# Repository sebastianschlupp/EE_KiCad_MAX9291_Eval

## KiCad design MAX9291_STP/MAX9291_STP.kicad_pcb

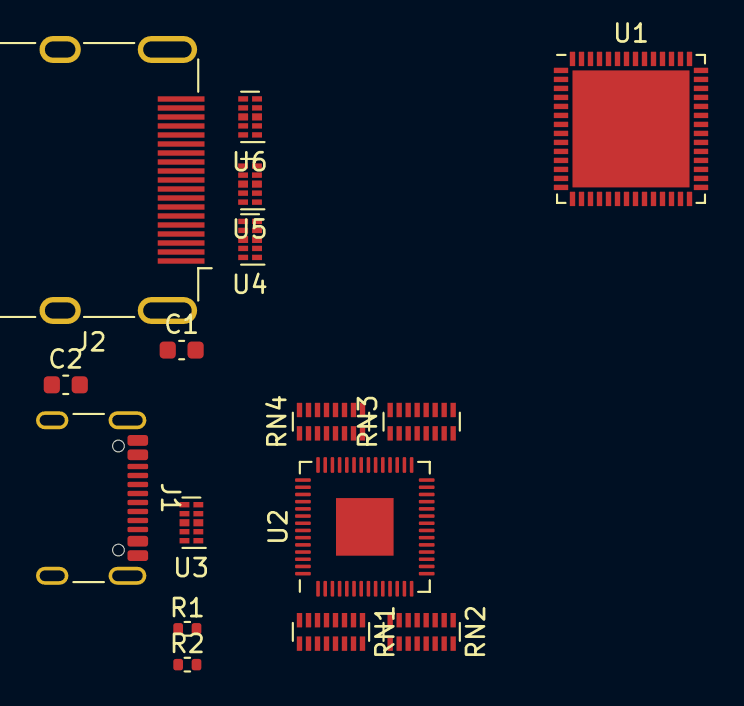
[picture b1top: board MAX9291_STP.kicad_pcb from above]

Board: 2 copper layers, 16 parts (0 on the bottom side), 53 nets, no tracks yet.

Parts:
C1, C2: C; C_0603_1608Metric
J1: USB_C_Receptacle; USB_C_Receptacle_GCT_USB4105-xx-A_16P_TopMnt_Horizontal
J2: HDMI_A_1.4; HDMI_A_Molex_208658-1001_Horizontal
R1, R2: 5.1k; R_0402_1005Metric
RN1, RN2, RN3, RN4: 4.7K; Yageo_YC248
U1: MAX9291; TQFN-56-1EP_8x8mm_P0.5mm_EP6.5x6.5mm
U2: RP2040; QFN-56-1EP_7x7mm_P0.4mm_EP3.2x3.2mm
U3, U4, U5, U6: TPD4E02B04DQA; USON-10_2.5x1.0mm_P0.5mm

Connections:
GNDREF: C1.2, C2.2, J1.A1 (GND), J1.A12 (GND), J1.B1 (GND), J1.B12 (GND), J2.17 (GND), R1.2, R2.2, U1.57 (GND), U2.57 (GND), U3.3 (G), U3.8 (G), U4.3 (G), U4.8 (G), U5.3 (G), U5.8 (G), U6.3 (G), U6.8 (G)
unnamed: J1.A5 (CC1), R2.1
unnamed: J1.B5 (CC2), R1.1
unnamed: C2.1, J1.S1 (SHIELD)
unnamed: J2.18 (+5V), U6.4 (IO3), U6.7 (NC)
unnamed: J2.10 (CK+), U5.4 (IO3), U5.7 (NC)
unnamed: J2.12 (CK-), U5.5 (IO4), U5.6 (NC)
unnamed: C1.1, J2.2 (D2S), J2.5 (D1S), J2.8 (D0S), J2.11 (CKS), J2.SH
unnamed: J2.7 (D0+), U5.1 (IO1), U5.10 (NC)
unnamed: J2.9 (D0-), U5.2 (IO2), U5.9 (NC)
unnamed: J2.4 (D1+), U4.4 (IO3), U4.7 (NC)
unnamed: J2.6 (D1-), U4.5 (IO4), U4.6 (NC)
unnamed: J2.1 (D2+), U4.1 (IO1), U4.10 (NC)
unnamed: J2.3 (D2-), U4.2 (IO2), U4.9 (NC)
unnamed: J2.19 (HPD/HEAC-), U6.5 (IO4), U6.6 (NC)
unnamed: J2.15 (SCL), U6.1 (IO1), U6.10 (NC)
unnamed: J2.16 (SDA), U6.2 (IO2), U6.9 (NC)
unnamed: RN1.1 (R1.1), U2.9 (GPIO7)
unnamed: RN1.2 (R2.1), U2.8 (GPIO6)
unnamed: RN1.3 (R3.1), U2.7 (GPIO5)
unnamed: RN1.4 (R4.1), U2.6 (GPIO4)
unnamed: RN1.5 (R5.1), U2.5 (GPIO3)
unnamed: RN1.6 (R6.1), U2.4 (GPIO2)
unnamed: RN1.7 (R7.1), U2.3 (GPIO1)
unnamed: RN1.8 (R8.1), U2.2 (GPIO0)
unnamed: RN2.1 (R1.1), U2.18 (GPIO15)
unnamed: RN2.2 (R2.1), U2.17 (GPIO14)
unnamed: RN2.3 (R3.1), U2.16 (GPIO13)
unnamed: RN2.4 (R4.1), U2.15 (GPIO12)
unnamed: RN2.5 (R5.1), U2.14 (GPIO11)
unnamed: RN2.6 (R6.1), U2.13 (GPIO10)
unnamed: RN2.7 (R7.1), U2.12 (GPIO9)
unnamed: RN2.8 (R8.1), U2.11 (GPIO8)
unnamed: RN3.1 (R1.1), U2.35 (GPIO23)
unnamed: RN3.2 (R2.1), U2.34 (GPIO22)
unnamed: RN3.3 (R3.1), U2.32 (GPIO21)
unnamed: RN3.4 (R4.1), U2.31 (GPIO20)
unnamed: RN3.5 (R5.1), U2.30 (GPIO19)
unnamed: RN3.6 (R6.1), U2.29 (GPIO18)
unnamed: RN3.7 (R7.1), U2.28 (GPIO17)
unnamed: RN3.8 (R8.1), U2.27 (GPIO16)
unnamed: RN4.3 (R3.1), U2.41 (GPIO29_ADC3)
unnamed: RN4.4 (R4.1), U2.40 (GPIO28_ADC2)
unnamed: RN4.5 (R5.1), U2.39 (GPIO27_ADC1)
unnamed: RN4.6 (R6.1), U2.38 (GPIO26_ADC0)
unnamed: RN4.7 (R7.1), U2.37 (GPIO25)
unnamed: RN4.8 (R8.1), U2.36 (GPIO24)
unnamed: U2.23 (DVDD), U2.50 (DVDD)
unnamed: U2.1 (IOVDD), U2.10 (IOVDD), U2.22 (IOVDD), U2.33 (IOVDD), U2.42 (IOVDD), U2.49 (IOVDD)
unnamed: J1.A7 (D-), J1.B7 (D-), U2.46 (USB_DM), U3.5 (IO4), U3.6 (NC)
unnamed: J1.A6 (D+), J1.B6 (D+), U2.47 (USB_DP), U3.4 (IO3), U3.7 (NC)
unnamed: U3.2 (IO2), U3.9 (NC)
VBUS: J1.A4 (VBUS), J1.A9 (VBUS), J1.B4 (VBUS), J1.B9 (VBUS), U3.1 (IO1), U3.10 (NC)

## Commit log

2024-02-12 Delete ProjectSpecifics.bak
    mistakenly omitted from .gitignore
2024-02-12 Updated .gitignore Added *.bak
2024-02-12 Deleted .bak files
    Seigned-off-by: Sebastian Schlupp <sebastian.schlupp@gmail.com>
